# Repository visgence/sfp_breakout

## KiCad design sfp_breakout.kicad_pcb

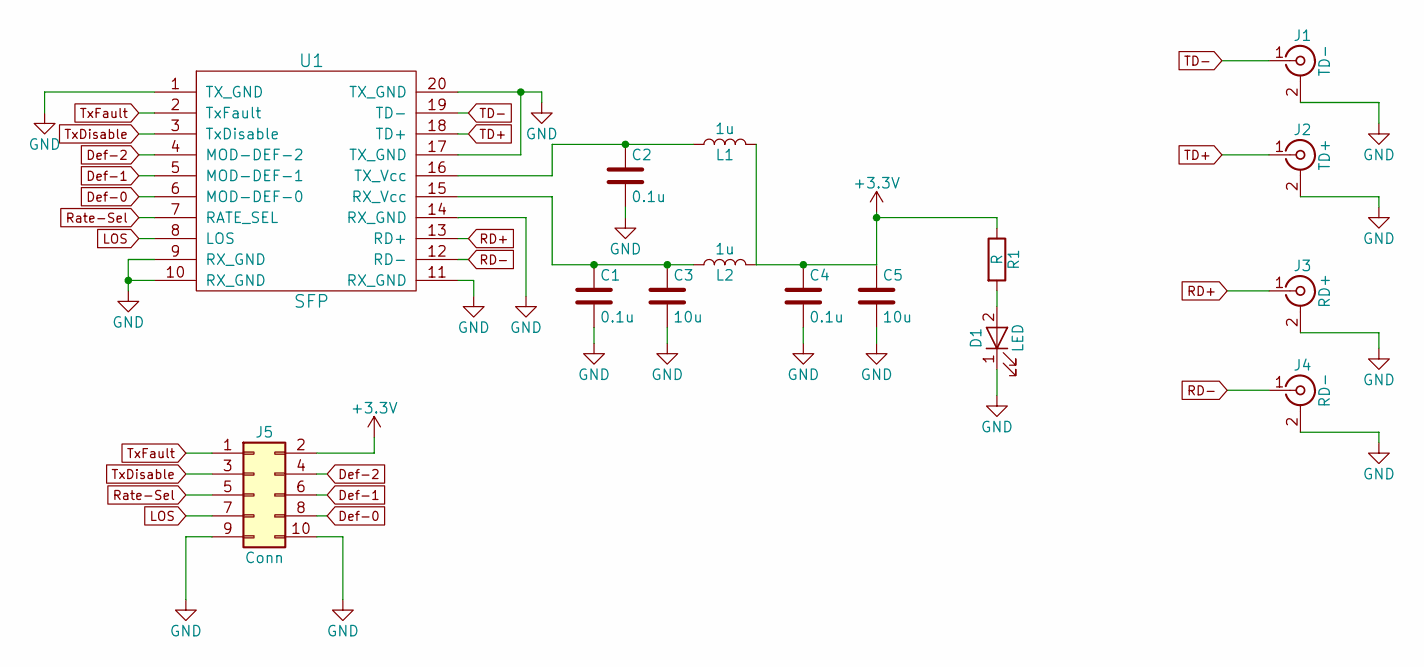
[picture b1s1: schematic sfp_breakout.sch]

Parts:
C1, C2, C4: 0.1u; C_0603
C3, C5: 10u; C_0603
D1: LED; LED_0603_HandSoldering
J1: TD-; CON-SMA-EDGE
J2: TD+; CON-SMA-EDGE
J3: RD+; CON-SMA-EDGE
J4: RD-; CON-SMA-EDGE
J5: Conn; Pin_Header_Straight_2x05_Pitch2.54mm
L1, L2: 1u; SM0603_VIS
R1: R; SM0603_VIS
U1: SFP; UE75-A20

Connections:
+3V3: C4.1, C5.1, J5.2, L1.2, L2.2, R1.1
Def-0: J5.8, U1.6 (MOD-DEF-0)
Def-1: J5.6, U1.5 (MOD-DEF-1)
Def-2: J5.4, U1.4 (MOD-DEF-2)
GND: C1.2, C2.2, C3.2, C4.2, C5.2, D1.1 (K), J1.2 (Ext), J2.2 (Ext), J3.2 (Ext), J4.2 (Ext), J5.9, J5.10, U1.1 (TX_GND), U1.9 (RX_GND), U1.10 (RX_GND), U1.11 (RX_GND), U1.14 (RX_GND), U1.17 (TX_GND), U1.20 (TX_GND), U1.
LOS: J5.7, U1.8 (LOS)
unnamed: C1.1, C3.1, L2.1, U1.15 (RX_Vcc)
unnamed: C2.1, L1.1, U1.16 (TX_Vcc)
unnamed: D1.2 (A), R1.2
RD+: J3.1 (In), U1.13 (RD+)
RD-: J4.1 (In), U1.12 (RD-)
Rate-Sel: J5.5, U1.7 (RATE_SEL)
TD+: J2.1 (In), U1.18 (TD+)
TD-: J1.1 (In), U1.19 (TD-)
TxDisable: J5.3, U1.3 (TxDisable)
TxFault: J5.1, U1.2 (TxFault)

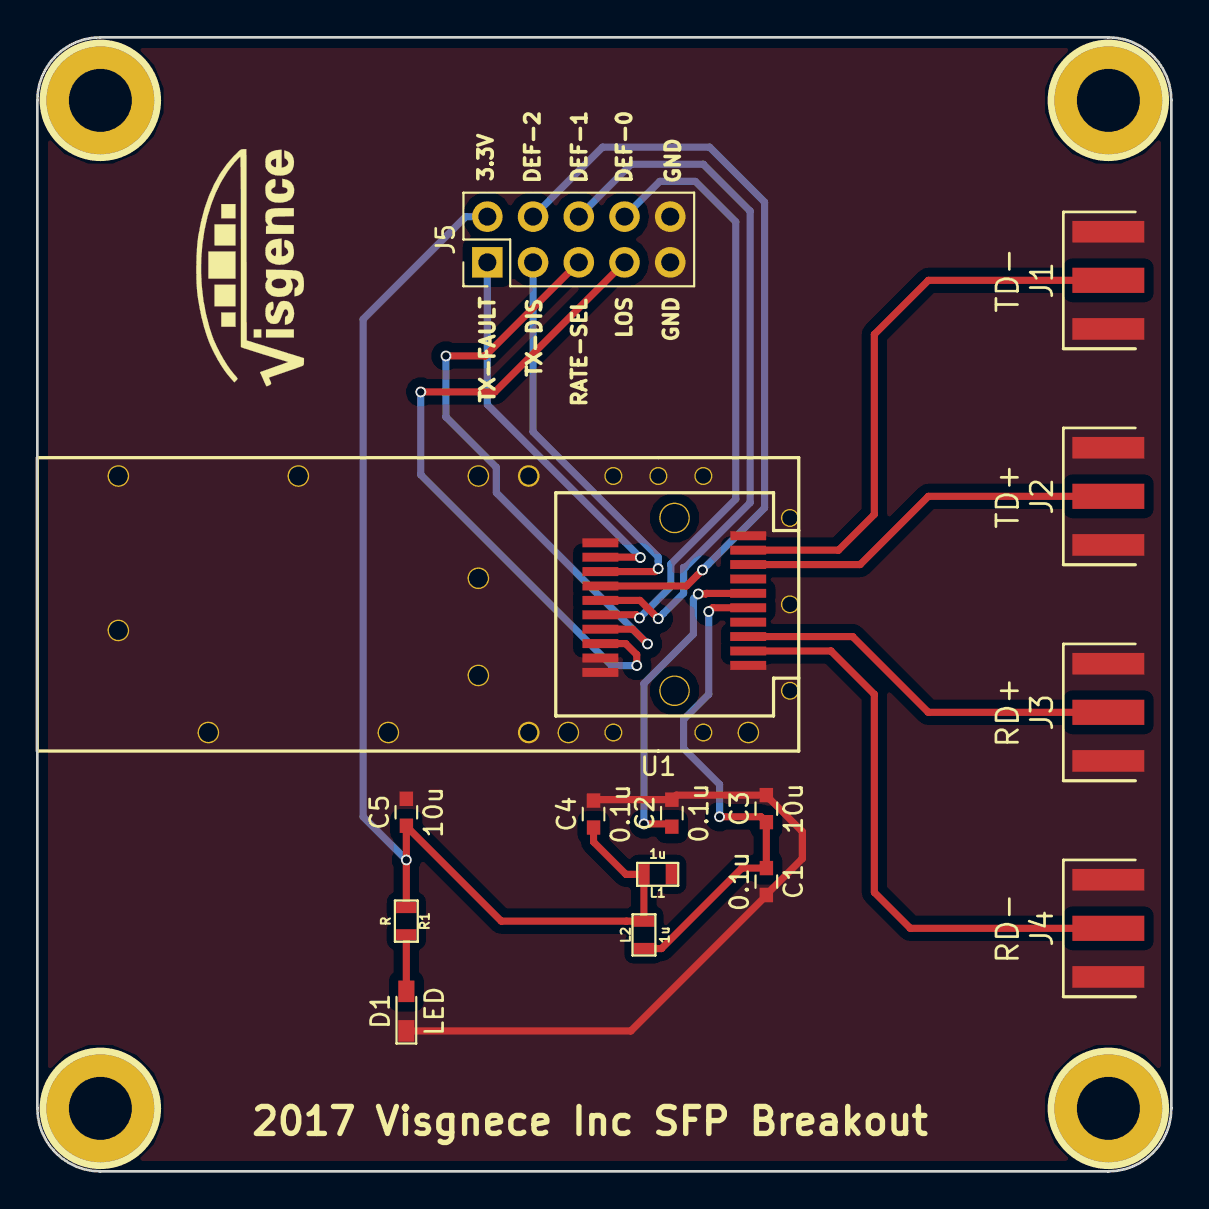
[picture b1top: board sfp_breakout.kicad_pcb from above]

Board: 2 copper layers, 63.0 x 63.0 mm, 19 parts (0 on the bottom side), 16 nets.

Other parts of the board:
h?: pin; 1pin_C
h?#2, h?#3, h?#4: pin; 1pin_C

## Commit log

2017-11-21 Added readme
2017-11-21 Started working on schematic
2017-11-21 Started some board layout
2017-11-30 Changed out SMA connector
2017-12-16 Added pin header, worked on board layout
2017-12-30 Did some layout and routing
2017-12-30 Did final routing, generated gerber files
